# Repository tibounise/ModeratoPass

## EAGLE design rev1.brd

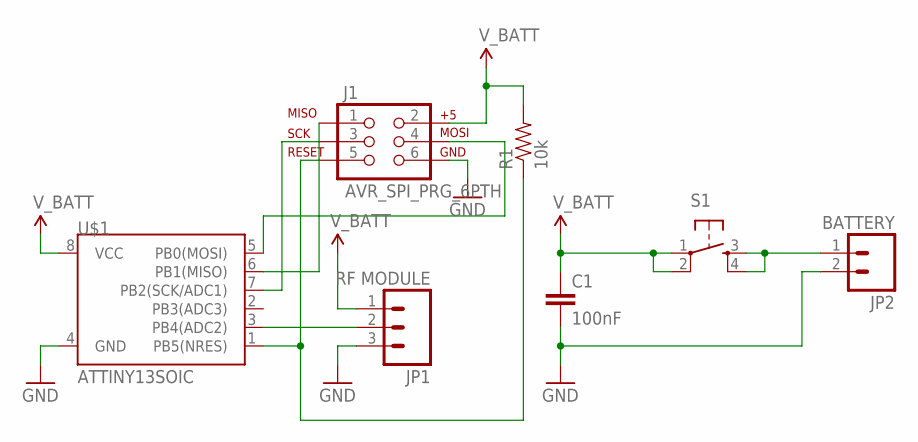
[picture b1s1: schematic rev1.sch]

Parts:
C1: 100nF; 1206
J1: AVR_SPI_PRG_6PTH; 2X3
JP1: RF MODULE; 1X03
JP2: BATTERY; 1X02
R1: 10k; 1206
S1: TAC_SWITCHPTH; TACTILE-PTH
U$1: ATTINY13SOIC; SO08

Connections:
GND: C1.2, J1.6, JP1.3, JP2.2, U$1.4 (GND)
unnamed: JP1.2, U$1.3 (PB4(ADC2))
unnamed: JP2.1, S1.3, S1.4
unnamed: J1.5, R1.1, U$1.1 (PB5(NRES))
unnamed: J1.3, U$1.7 (PB2(SCK/ADC1))
unnamed: J1.1, U$1.6 (PB1(MISO))
unnamed: J1.4, U$1.5 (PB0(MOSI))
V_BATT: C1.1, J1.2, JP1.1, R1.2, S1.1, S1.2, U$1.8 (VCC)

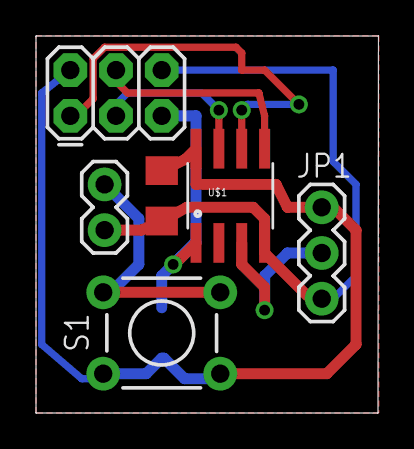
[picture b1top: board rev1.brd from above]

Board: 2 copper layers, 19.0 x 20.9 mm, 7 parts (1 on the bottom side), 8 nets.

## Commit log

2014-12-27 Modifying things to get them working on AtMega1284p

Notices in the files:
parts and their libraries:
SparkFun-Capacitors: Licensing: Creative Commons ShareAlike 4.0 International - https://creativecommons.org/licenses/by-sa/4.0
